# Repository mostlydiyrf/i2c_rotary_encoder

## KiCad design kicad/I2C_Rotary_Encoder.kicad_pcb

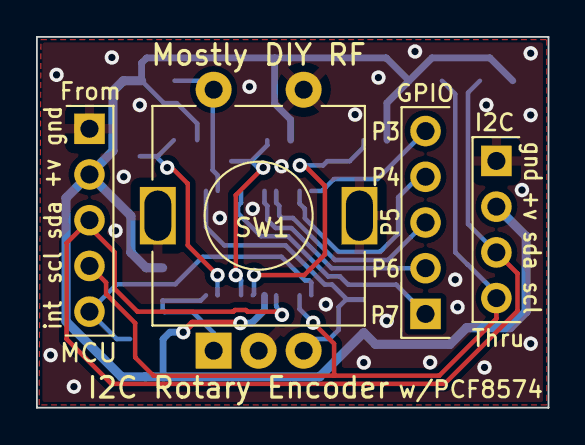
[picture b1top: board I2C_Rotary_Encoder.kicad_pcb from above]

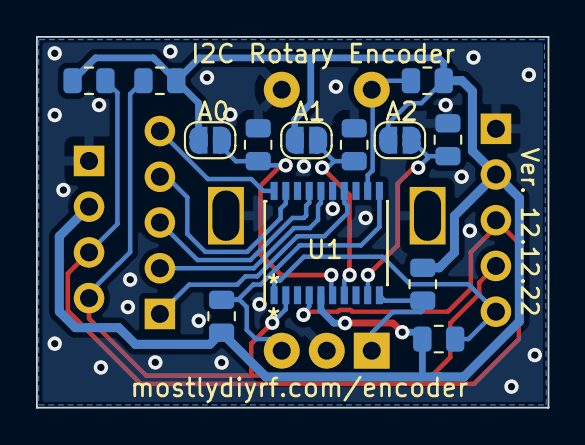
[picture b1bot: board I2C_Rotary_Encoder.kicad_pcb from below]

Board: 2 copper layers, 28.4 x 20.6 mm, 17 parts (13 on the bottom side), 16 nets.

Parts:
J1, J2: Conn_01x05; PinHeader_1x05_P2.54mm_Vertical
J3: Conn_01x04; PinHeader_1x04_P2.54mm_Vertical
JP1, JP2, JP3: SolderJumper_2_Open; SolderJumper-2_P1.3mm_Open_RoundedPad1.0x1.5mm
R1, R2, R3, R4, R5, R6, R7, R8, R9: 10K; R_0805_2012Metric
SW1: RotaryEncoder_Switch; RotaryEncoder_Alps_EC11E-Switch_Vertical_H20mm
U1: PCF8574A; SSOP-20_4.4x6.5mm_P0.65mm

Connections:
/INT: J1.5, R9.2, U1.1 (~INT)
/SCL: J1.4, J3.4, R8.2, U1.2 (SCL)
/SDA: J1.3, J3.3, R7.2, U1.4 (SDA)
A0: JP3.2 (B), R6.1, U1.6 (A0)
A1: JP2.2 (B), R5.1, U1.7 (A1)
A2: JP1.2 (B), R4.1, U1.9 (A2)
GND: J1.1, J3.1, R4.2, R5.2, R6.2, SW1.C, SW1.MP, SW1.S1, U1.15 (VSS)
unnamed: J2.1, U1.14 (P3)
unnamed: J2.2, U1.16 (P4)
unnamed: J2.3, U1.17 (P5)
unnamed: J2.4, U1.19 (P6)
unnamed: J2.5, U1.20 (P7)
unnamed: R1.2, SW1.A, U1.10 (P0)
unnamed: R2.2, SW1.B, U1.11 (P1)
unnamed: R3.2, SW1.S2, U1.12 (P2)
VDD: J1.2, J3.2, JP1.1 (A), JP2.1 (A), JP3.1 (A), R1.1, R2.1, R3.1, R7.1, R8.1, R9.1, U1.5 (VDD)
